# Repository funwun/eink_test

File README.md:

# eink_test
some hardware and firmware to run a battery-powered electronic ink display

This is a NOT WORKING project with several known issues and quite likely unknown ones too.

USE DATA AT YOUR OWN RISK!

Three known hardware issues are a pinout problem with the 39 pin eink display connector, a PIC bpyass capacitor connection error, and an RX-TX swap issue with the bluetooth module.  Plus the code doesn't work.

This project was intended to be a quick layout-and-firmware operation based on projects at http://essentialscrap.com/eink/index.html and http://spritesmods.com/?art=einkdisplay.  I bit off more than I could chew for a weekend project however.

The purpose of uploading this to the internet is soley to ask for help fixing things, not to display a working good project.  Possibly may be fixed in the future but it is a sort of whimsical, should-be-fun project so all bets are off.

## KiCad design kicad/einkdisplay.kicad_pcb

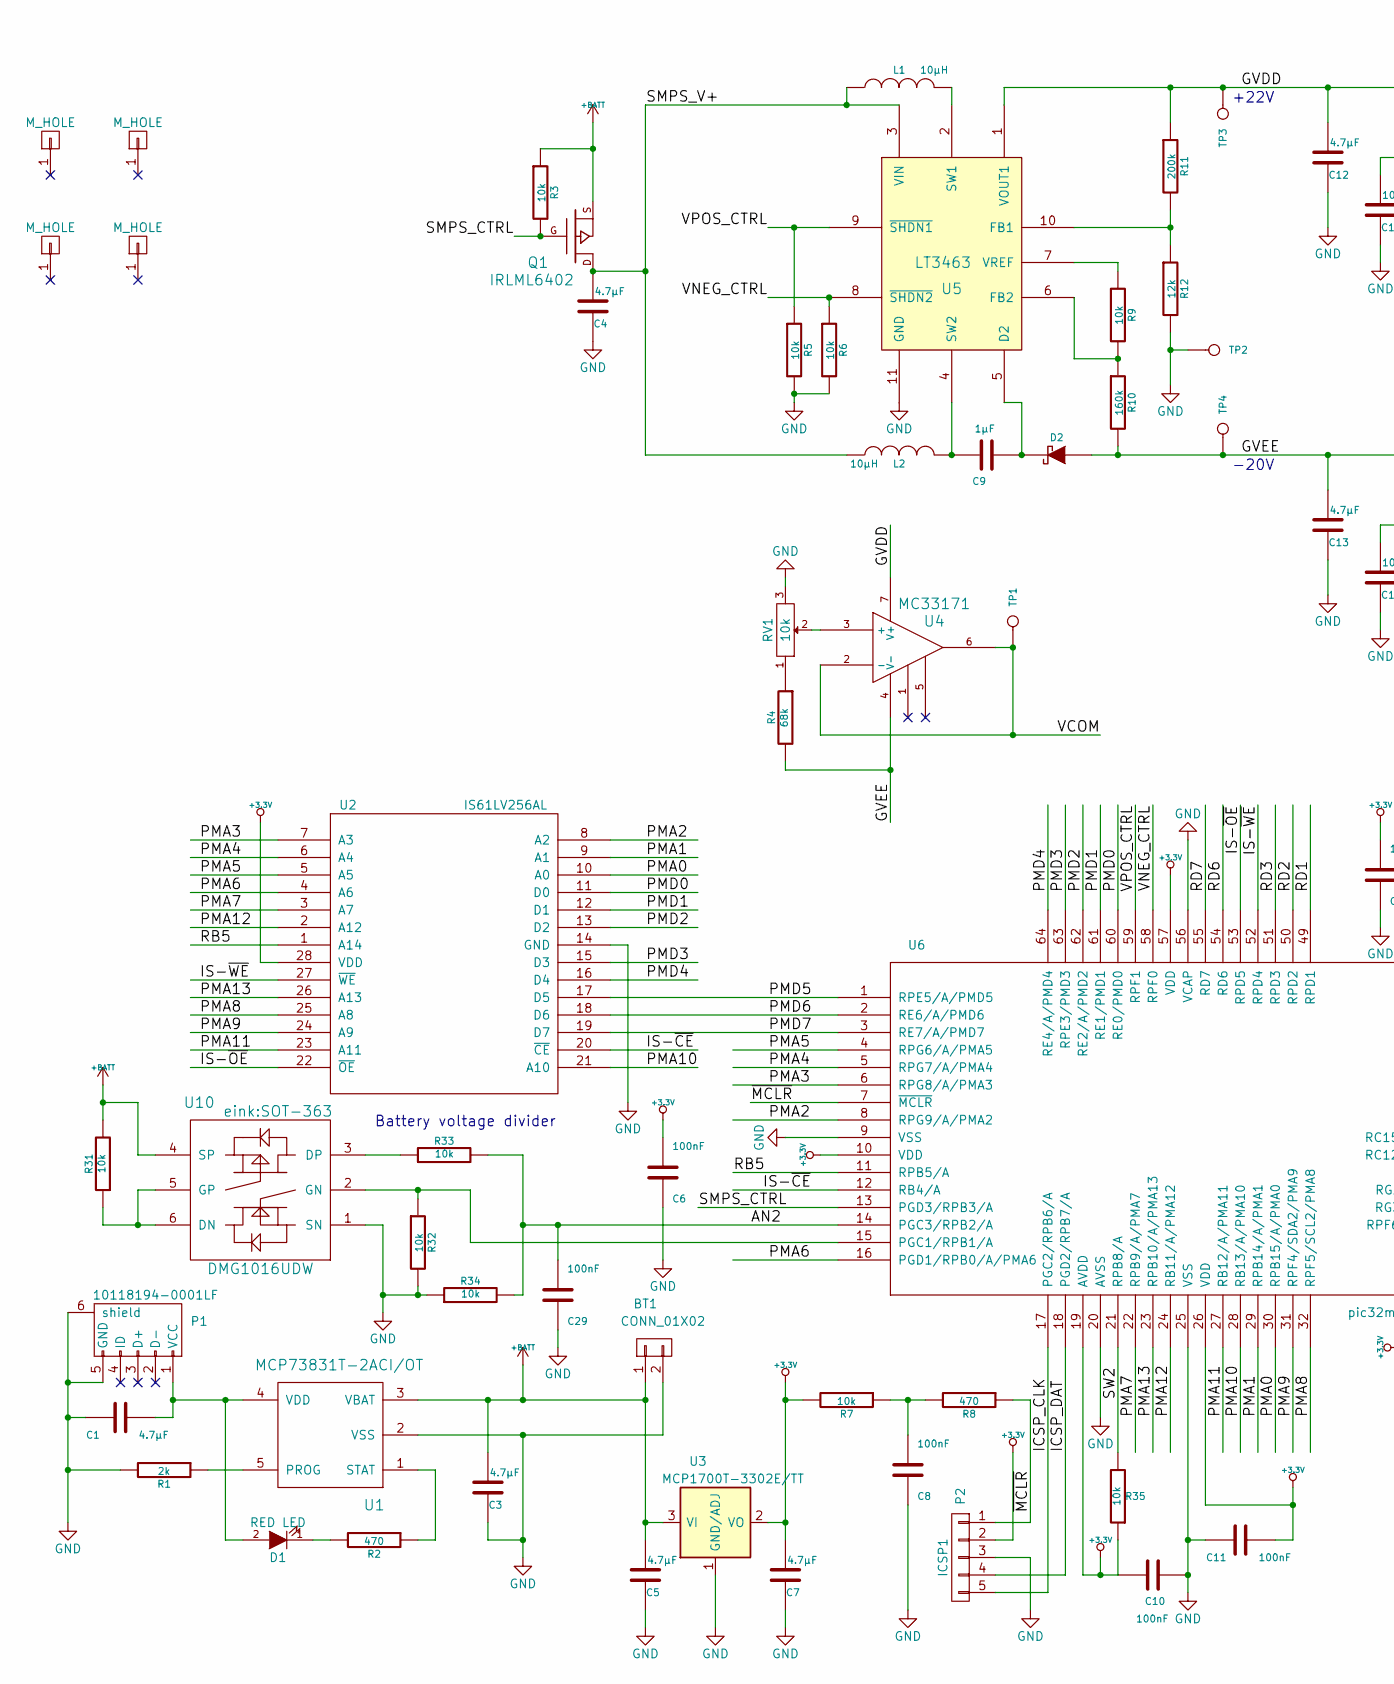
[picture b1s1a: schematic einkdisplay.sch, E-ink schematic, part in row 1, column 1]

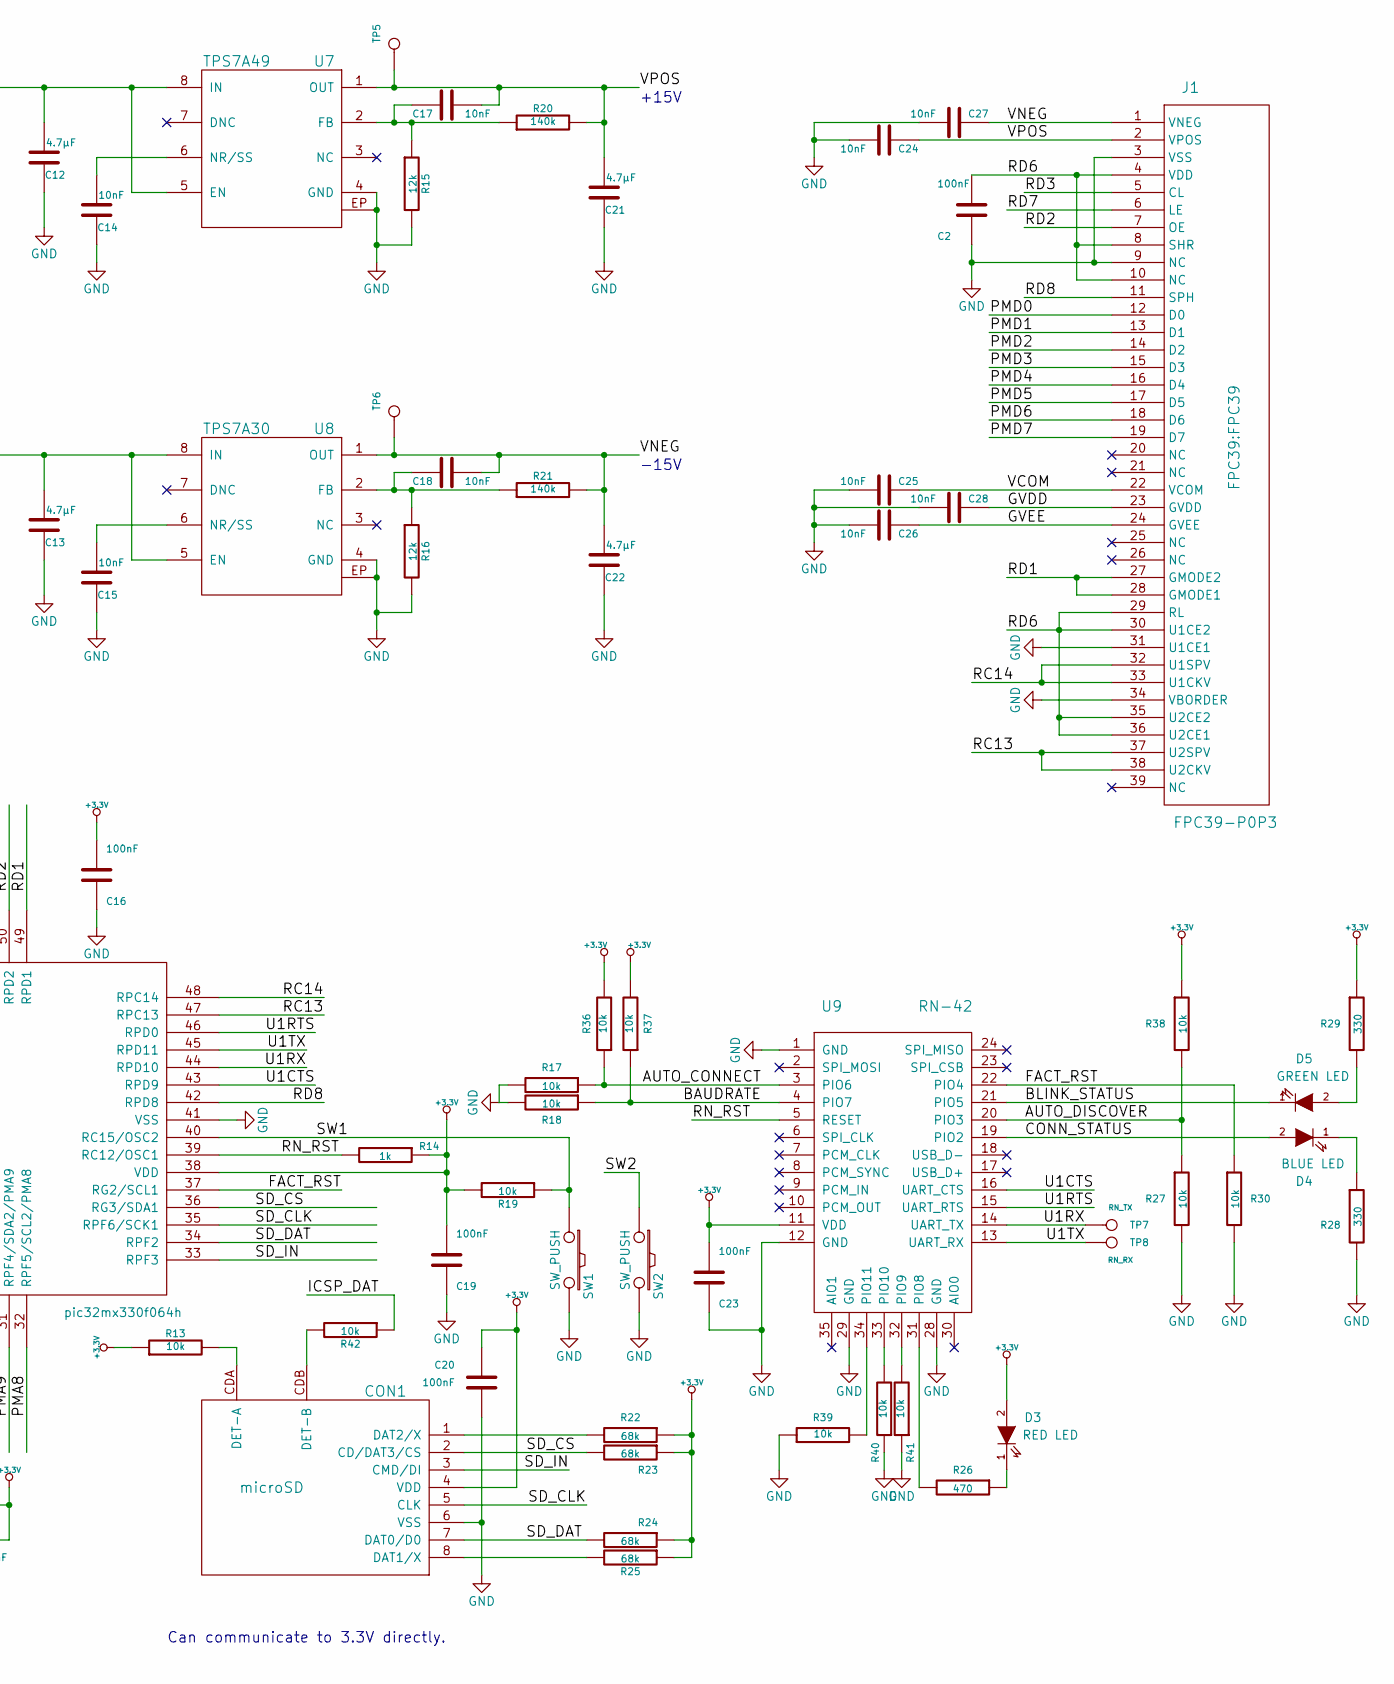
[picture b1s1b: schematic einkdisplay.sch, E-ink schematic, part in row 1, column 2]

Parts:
BT1: CONN_01X02; PINHEAD1-2
C1, C3, C4, C5, C7, C12, C13, C21, C22: 4.7µF; C_1206; Rating 50V; MFG_PN UMK316AB7475KL-T
C2, C6, C8, C10, C11, C16, C19, C20, C23, C29: 100nF; C_0603
C9: 1µF; C_0805; Rating 50V; MFG_PN GRM219R61H105KA73D
C14, C15, C17, C18, C24, C25, C26, C27, C28: 10nF; C_0603; Rating 50V; MFG_PN GRM188R71H103KA01D
CON1: microSD; microSD_std_top; MFG_PN DM3AT-SF-PEJM5
D1, D3: RED LED; LED-0603
D2: DIODESCH; SOD-323-inv; MFG_PN 1N4148WX-TP
D4: BLUE LED; LED-0603
D5: GREEN LED; LED-0603
J1: FPC39-P0P3; FPC39; MFG_PN FH26-39S-0.3SHW(05)
L1, L2: 10µH; NR4018_HandSoldering; MFG_PN LQH44PN100MP0L
MH1, MH2, MH3, MH4: M_HOLE; MountingHole_3mm
P1: 10118194-0001LF; USB_Micro-B; MFG_PN 10118194-0001LF
P2: ICSP1; Pin_Header_Straight_1x05
Q1: 3A; SOT-23_IRLML6402; MFG_PN IRLML6402
R1: 2k; R_0603
R2, R8, R26: 470; R_0603
R3, R5, R6, R7, R9, R13, R17, R18, R19, R27, R30, R31, R32, R33, R34, R35, R36, R37, R38, R39, R40, R41, R42: 10k; R_0603
R4, R22, R23, R24, R25: 68k; R_0603
R10: 160k; R_0603
R11: 200k; R_0603
R12, R15, R16: 12k; R_0603
R14: 1k; R_0603
R20, R21: 140k; R_0603
R28, R29: 330; R_0603
RV1: 10k; POT_SMD; MFG_PN 3314G-1-103E
SW1, SW2: SW_PUSH; SW_SPST_PTS645; MFG_PN PTS645SM43SMTR92 LFS
TP1: VCOM; PINTST
TP2: GND; PINTST
TP3: +22V; PINTST
TP4: -20V; PINTST
TP5: +15V; PINTST
TP6: -15V; PINTST
TP7: RN_TX; PINTST
TP8: RN_RX; PINTST
U1: MCP73831T-2ACI/OT; SOT-23-5
U2: IS61LV256AL; 28TSOP-I; MFG_PN IS61LV256AL-10TLI
U3: MCP1700T-3302E/TT; SOT-23
U4: MC33171; SOIC-8_3.9x4.9mm_Pitch1.27mm; MFG_PN MC33171DT
U5: LT3463; 10DFN-3x3; MFG_PN LT3463EDD#PBF
U6: pic32mx330f064h; LQFP-64_10x10mm_Pitch0.5mm
U7: TPS7A49; 8MSOP; MFG_PN TPS7A4901DGNR
U8: TPS7A30; 8MSOP; MFG_PN TPS7A3001DGNR
U9: RN-42; RN-41; MFG_PN RN42-I/RM
U10: DMG1016UDW; SOT-363; MFG_PN DMG1016UDW-7

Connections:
+3.3V: C6.1, C7.1, C10.2, C11.1, C16.1, C19.1, C20.2, C23.1, CON1.4 (VDD), D3.2 (A), P2.2, R7.2, R13.1, R14.1, R19.2, R22.1, R23.1, R24.1, R25.1, R29.1, R35.1, R36.2, R37.2, R38.1, U2.28 (VDD), U3.2 (VO), U6.10 (VDD), U6.19 (AVDD), U6.26 (VDD), U6.38 (VDD), U6.57 (VDD), U9.11 (VDD); also elsewhere on the board
+BATT: BT1.1, C3.1, C5.1, Q1.S, R3.1, R31.2, U1.3 (VBAT), U3.3 (VI), U10.4 (SP)
/AN2: C29.1, R33.2, R34.2, U6.14 (PGC3/RPB2/A)
/AUTO_CONNECT: R17.1, R36.1, U9.3 (PIO6)
/AUTO_DISCOVER: R27.1, R38.2, U9.20 (PIO3)
/BAUDRATE: R18.1, R37.1, U9.4 (PIO7)
/BLINK_STATUS: D5.1 (K), U9.21 (PIO5); also elsewhere on the board
/CONN_STATUS: D4.2 (A), U9.19 (PIO2); also elsewhere on the board
/FACT_RST: R30.1, U6.37 (RG2/SCL1), U9.22 (PIO4)
/GVDD: C12.1, C28.2, J1.23 (GVDD), R11.1, TP3.1, U4.7 (V+), U5.1 (VOUT1), U7.5 (EN), U7.8 (IN)
/GVEE: C13.1, C26.2, D2.1 (A), J1.24 (GVEE), R4.2, R10.2, TP4.1, U4.4 (V-), U8.5 (EN), U8.8 (IN)
/ICSP_CLK: P2.5, U6.17 (PGC2/RPB6/A)
/ICSP_DAT: P2.4, R42.1, U6.18 (PGD2/RPB7/A)
/IS-~CE: U2.20 (~CE), U6.12 (RB4/A)
/IS-~OE: U2.22 (~OE), U6.53 (RPD5)
/IS-~WE: U2.27 (~WE), U6.52 (RPD4)
/PMA0: U2.10 (A0), U6.30 (RPB15/A/PMA0)
/PMA1: U2.9 (A1), U6.29 (RPB14/A/PMA1)
/PMA2: U2.8 (A2), U6.8 (RPG9/A/PMA2)
/PMA3: U2.7 (A3), U6.6 (RPG8/A/PMA3)
/PMA4: U2.6 (A4), U6.5 (RPG7/A/PMA4)
/PMA5: U2.5 (A5), U6.4 (RPG6/A/PMA5)
/PMA6: U2.4 (A6), U6.16 (PGD1/RPB0/A/PMA6)
/PMA7: U2.3 (A7), U6.22 (RPB9/A/PMA7)
/PMA8: U2.25 (A8), U6.32 (RPF5/SCL2/PMA8)
/PMA9: U2.24 (A9), U6.31 (RPF4/SDA2/PMA9)
/PMA10: U2.21 (A10), U6.28 (RB13/A/PMA10)
/PMA11: U2.23 (A11), U6.27 (RB12/A/PMA11)
/PMA12: U2.2 (A12), U6.24 (RB11/A/PMA12)
/PMA13: U2.26 (A13), U6.23 (RPB10/A/PMA13)
/PMD0: J1.12 (D0), U2.11 (D0), U6.60 (RE0/PMD0)
/PMD1: J1.13 (D1), U2.12 (D1), U6.61 (RE1/PMD1)
/PMD2: J1.14 (D2), U2.13 (D2), U6.62 (RE2/A/PMD2)
/PMD3: J1.15 (D3), U2.15 (D3), U6.63 (RPE3/PMD3)
/PMD4: J1.16 (D4), U2.16 (D4), U6.64 (RE4/A/PMD4)
/PMD5: J1.17 (D5), U2.17 (D5), U6.1 (RPE5/A/PMD5)
/PMD6: J1.18 (D6), U2.18 (D6), U6.2 (RE6/A/PMD6)
/PMD7: J1.19 (D7), U2.19 (D7), U6.3 (RE7/A/PMD7)
/RB5: U2.1 (A14), U6.11 (RPB5/A)
/RC13: J1.37 (U2SPV), J1.38 (U2CKV), U6.47 (RPC13)
/RC14: J1.32 (U1SPV), J1.33 (U1CKV), U6.48 (RPC14)
/RD1: J1.27 (GMODE2), J1.28 (GMODE1), U6.49 (RPD1)
/RD2: J1.7 (OE), U6.50 (RPD2)
/RD3: J1.5 (CL), U6.51 (RPD3)
/RD6: C2.1, J1.4 (VDD), J1.8 (SHR), J1.10 (NC), J1.29 (RL), J1.30 (U1CE2), J1.35 (U2CE2), J1.36 (U2CE1), U6.54 (RD6)
/RD7: J1.6 (LE), U6.55 (RD7)
/RD8: J1.11 (SPH), U6.42 (RPD8)
/RN_RST: R14.2, U6.39 (RC12/OSC1), U9.5 (RESET)
/SD_CLK: CON1.5 (CLK), U6.35 (RPF6/SCK1)
/SD_CS: CON1.2 (CD/DAT3/CS), R23.2, U6.36 (RG3/SDA1)
/SD_DAT: CON1.7 (DAT0/D0), R24.2, U6.34 (RPF2)
/SD_IN: CON1.3 (CMD/DI), U6.33 (RPF3)
/SMPS_CTRL: Q1.G, R3.2, U6.13 (PGD3/RPB3/A)
/SMPS_V+: C4.1, L1.1, L2.1, Q1.D, U5.3 (VIN)
/SW1: R19.1, SW1.1, U6.40 (RC15/OSC2); also elsewhere on the board
/SW2: R35.2, SW2.1, U6.21 (RPB8/A); also elsewhere on the board
/U1CTS: U6.43 (RPD9), U9.16 (UART_CTS)
/U1RTS: U6.46 (RPD0), U9.15 (UART_RTS)
/VCOM: C25.2, J1.22 (VCOM), TP1.1, U4.2 (-), U4.6
/VNEG: C18.1, C22.1, C27.2, J1.1 (VNEG), R21.2, TP6.1, U8.1 (OUT)
/VNEG_CTRL: R6.1, U5.8 (~SHDN2), U6.58 (RPF0)
/VPOS: C17.1, C21.1, C24.2, J1.2 (VPOS), R20.2, TP5.1, U7.1 (OUT)
/VPOS_CTRL: R5.1, U5.9 (~SHDN1), U6.59 (RPF1)
/~MCLR: P2.1, R8.1, U6.7 (~MCLR)
GND: BT1.2, C1.2, C2.2, C3.2, C4.2, C5.2, C6.2, C7.2, C8.2, C10.1, C11.2, C12.2, C13.2, C14.2, C15.2, C16.2, C19.2, C20.1, C21.2, C22.2, C23.2, C24.1, C25.1, C26.1, C27.1, C28.1, C29.2, CON1.6 (VSS), J1.3 (VSS), J1.9 (NC), J1.31 (U1CE1), J1.34 (VBORDER), P1.5 (GND), P1.6 (shield), P2.3, R1.2, R5.2, R6.2, R12.2, R15.2, R16.2, R17.2, R18.2, R27.2, R28.2, R30.2, R32.2, R34.1, R39.1, R40.1, R41.1, RV1.3, SW1.2, SW2.2, TP2.1, U1.2 (VSS), U2.14 (GND), U3.1 (GND/ADJ), U5.11 (GND), U6.9 (VSS), U6.20 (AVSS), U6.25 (VSS), U6.41 (VSS), U6.56 (VCAP), U7.4 (GND), U7.EP, U8.4 (GND), U8.EP, U9.1 (GND), U9.12 (GND), U9.28 (GND), U9.29 (GND), U10.1 (SN); also elsewhere on the board
unnamed 65: C1.1, D1.2 (A), P1.1 (VCC), U1.4 (VDD); also elsewhere on the board
unnamed: C8.1, R7.1, R8.2
unnamed: C9.1, L2.2, U5.4 (SW2)
unnamed: C9.2, D2.2 (K), U5.5 (D2)
unnamed: C14.1, U7.6 (NR/SS)
unnamed: C15.1, U8.6 (NR/SS)
unnamed: C17.2, R15.1, R20.1, U7.2 (FB)
unnamed: C18.2, R16.1, R21.1, U8.2 (FB)
unnamed: CON1.1 (DAT2/X), R22.2
unnamed: CON1.8 (DAT1/X), R25.2
unnamed: CON1.CDA (DET-A), R13.2
unnamed: CON1.CDB (DET-B), R42.2
unnamed 77: D1.1 (K), R2.2; also elsewhere on the board
unnamed 78: D3.1 (K), R26.1; also elsewhere on the board
unnamed 79: D4.1 (K), R28.1; also elsewhere on the board
unnamed 80: D5.2 (A), R29.2; also elsewhere on the board
unnamed: L1.2, U5.2 (SW1)
unnamed: R1.1, U1.5 (PROG)
unnamed: R2.1, U1.1 (STAT)
unnamed: R4.1, RV1.1
unnamed: R9.1, U5.7 (VREF)
unnamed: R9.2, R10.1, U5.6 (FB2)
unnamed: R11.2, R12.1, U5.10 (FB1)
unnamed: R26.2, U9.31 (PIO8)
unnamed: R31.1, U10.5 (GP), U10.6 (DN)
unnamed: R32.1, U6.15 (PGC1/RPB1/A), U10.2 (GN)
unnamed: R33.1, U10.3 (DP)
unnamed: R39.2, U9.34 (PIO11)
unnamed: R40.2, U9.33 (PIO10)
unnamed: R41.2, U9.32 (PIO9)
unnamed: RV1.2, U4.3 (+)

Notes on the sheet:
+15V
-15V
-20V
+22V
Can communicate to 3.3V directly.
Battery voltage divider

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
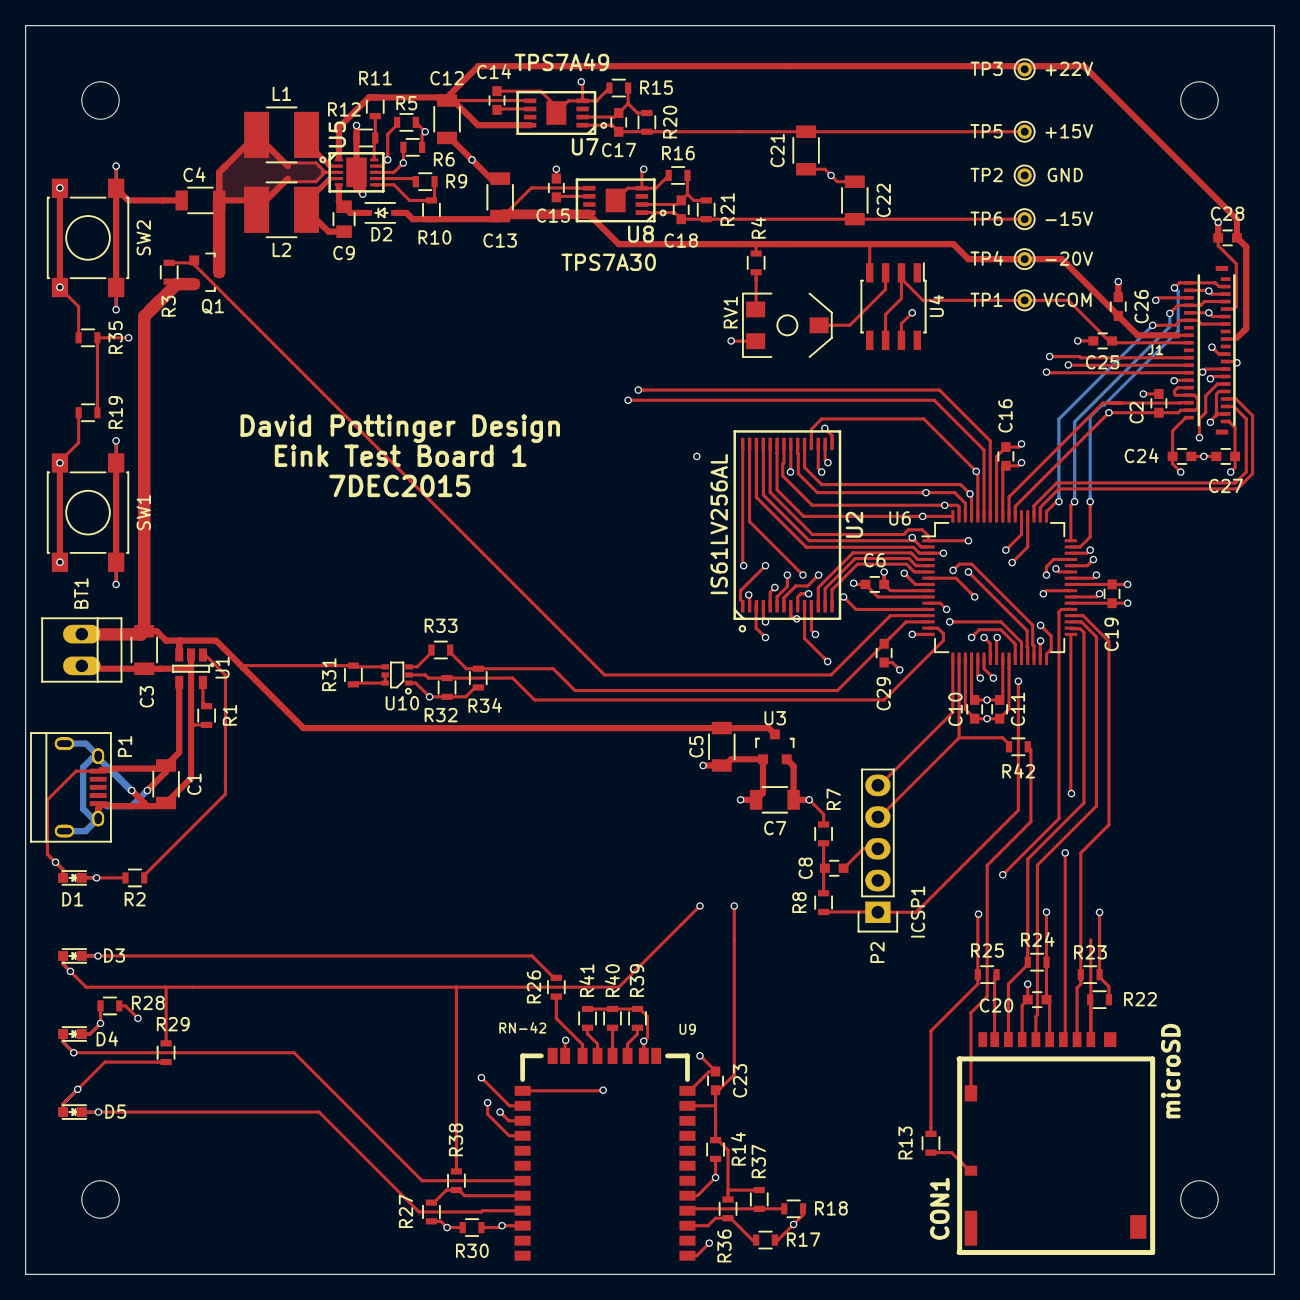
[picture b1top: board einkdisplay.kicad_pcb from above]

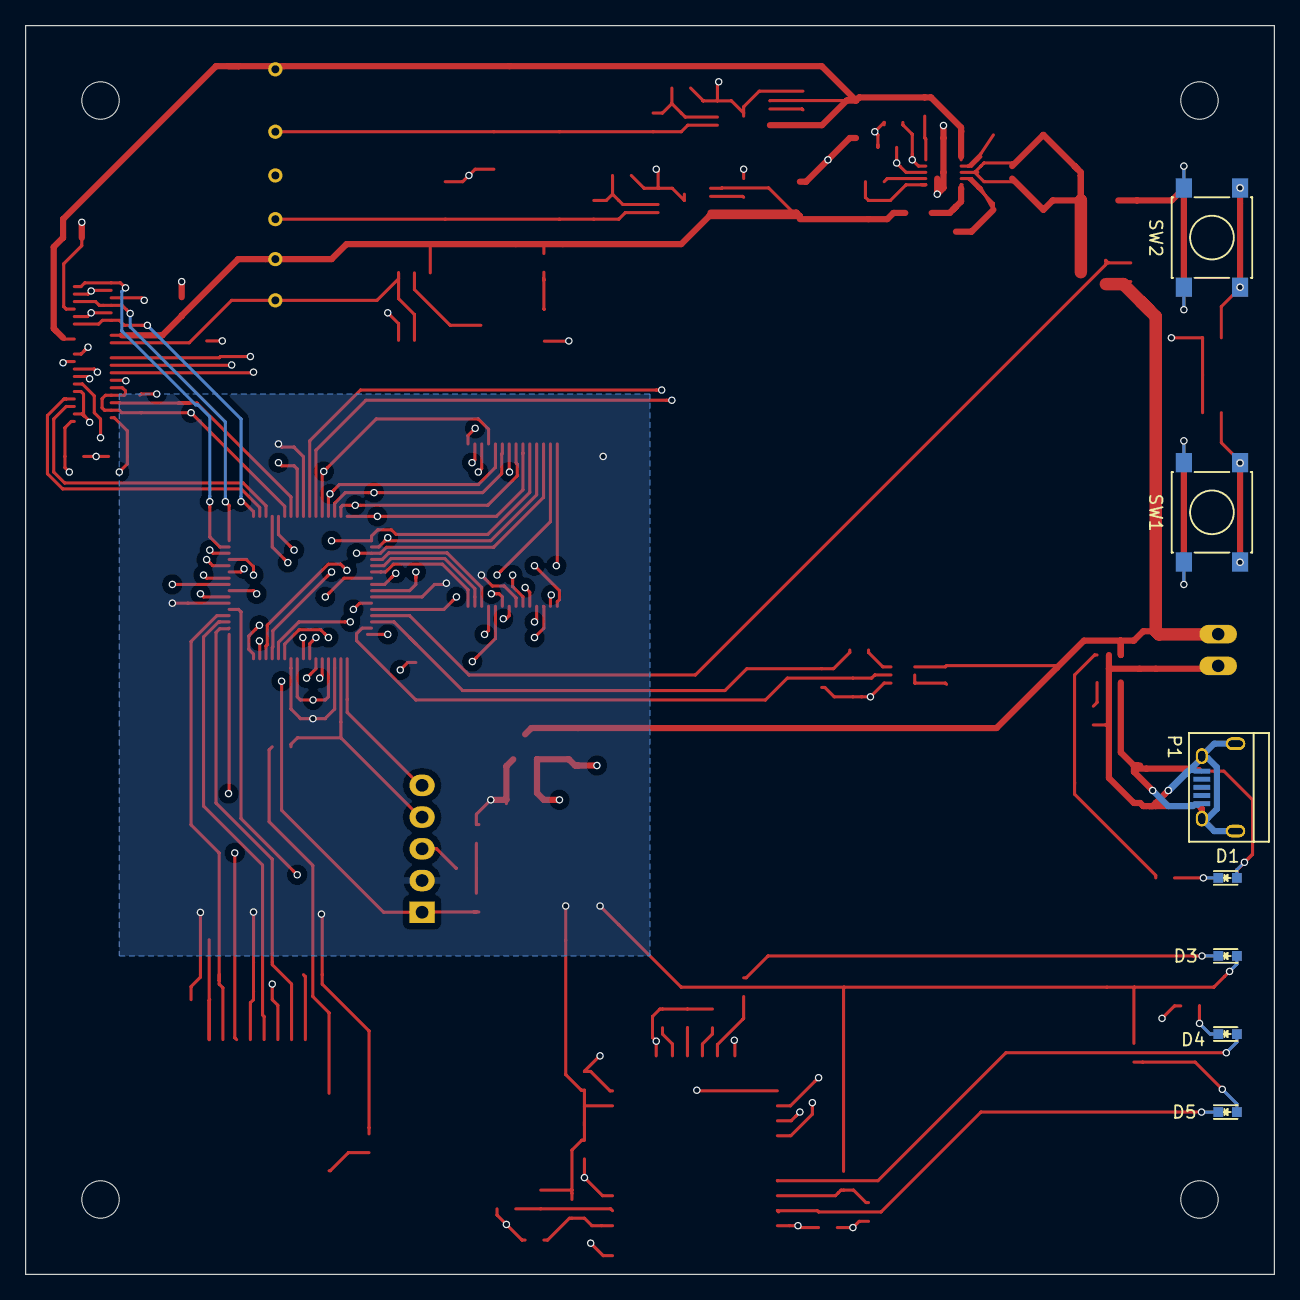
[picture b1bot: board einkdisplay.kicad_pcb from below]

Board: 4 copper layers, 100.0 x 100.0 mm, 114 parts (7 on the bottom side), 98 nets.

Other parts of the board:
D1#2, D3#2: RED LED; LED-0603
D4#2: BLUE LED; LED-0603
D5#2: GREEN LED; LED-0603
P1#2: 10118194-0001LF; USB_Micro-B
SW1#2, SW2#2: SW_PUSH; SW_SPST_PTS645

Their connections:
+3.3V: D3#2.2; also elsewhere on the board
/BLINK_STATUS: D5#2.1; also elsewhere on the board
/CONN_STATUS: D4#2.2; also elsewhere on the board
/SW1: SW1#2.1; also elsewhere on the board
/SW2: SW2#2.1; also elsewhere on the board
GND: P1#2.5, P1#2.6, SW1#2.2, SW2#2.2; also elsewhere on the board
unnamed 65: D1#2.2, P1#2.1; also elsewhere on the board
unnamed 77: D1#2.1; also elsewhere on the board
unnamed 78: D3#2.1; also elsewhere on the board
unnamed 79: D4#2.1; also elsewhere on the board
unnamed 80: D5#2.2; also elsewhere on the board
